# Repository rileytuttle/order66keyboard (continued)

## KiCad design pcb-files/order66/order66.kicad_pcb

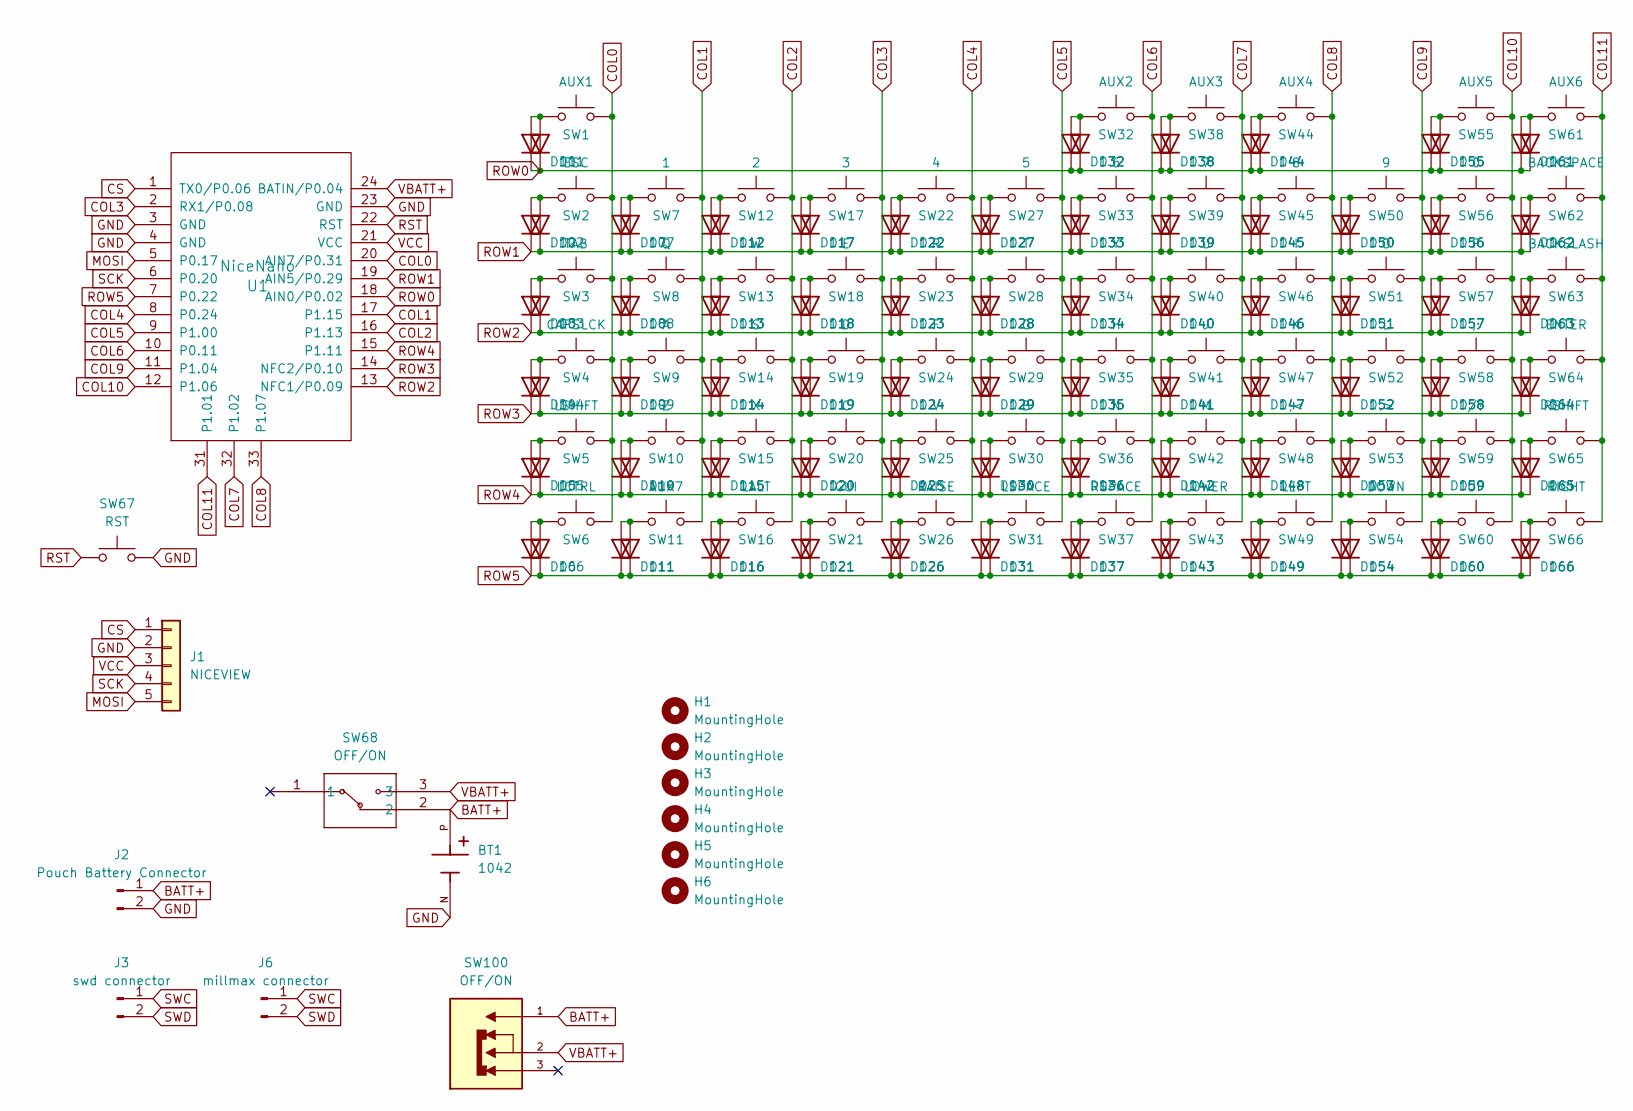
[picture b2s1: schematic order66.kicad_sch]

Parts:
BT1: 1042; BAT_1043P; PARTREV D
D1, D2, D3, D4, D5, D6, D7, D8, D9, D10, D11, D12, D13, D14, D15, D16, D17, D18, D19, D20, D21, D22, D23, D24, D25, D26, D27, D28, D29, D30, D31, D32, D33, D34, D35, D36, D37, D38, D39, D40, D41, D42, D43, D44, D45, D46, D47, D48, D49, D50, D51, D52, D53, D54, D55, D56, D57, D58, D59, D60, D61, D62, D63, D64, D65, D66: 1N4148; D_DO-35_SOD27_P7.62mm_Horizontal
D101, D102, D103, D104, D105, D106, D107, D108, D109, D110, D111, D112, D113, D114, D115, D116, D117, D118, D119, D120, D121, D122, D123, D124, D125, D126, D127, D128, D129, D130, D131, D132, D133, D134, D135, D136, D137, D138, D139, D140, D141, D142, D143, D144, D145, D146, D147, D148, D149, D150, D151, D152, D153, D154, D155, D156, D157, D158, D159, D160, D161, D162, D163, D164, D165, D166: 1N4148; D_SOD-123
H1, H2, H3, H4, H5, H6: MountingHole; MountingHole_2.7mm_M2.5
J1: NICEVIEW; PinHeader_1x05_P2.54mm_Vertical
J2: Pouch Battery Connector; JST_PH_B2B-PH-K_1x02_P2.00mm_Vertical
J3: swd connector; PinHeader_1x02_P2.54mm_Horizontal
J6: millmax connector; PinHeader_1x02_P2.54mm_Vertical
SW1: AUX1; MX-Hotswap-1U
SW2: ESC; MX-Hotswap-1U
SW3: TAB; MX-Hotswap-1U
SW4: CAPSLCK; MX-Hotswap-1U
SW5: LSHIFT; MX-Hotswap-1U
SW6: LCTRL; MX-Hotswap-1U
SW7: 1; MX-Hotswap-1U
SW8: Q; MX-Hotswap-1U
SW9: A; MX-Hotswap-1U
SW10: Z; MX-Hotswap-1U
SW11: AUX7; MX-Hotswap-1U
SW12: 2; MX-Hotswap-1U
SW13: W; MX-Hotswap-1U
SW14: S; MX-Hotswap-1U
SW15: X; MX-Hotswap-1U
SW16: LALT; MX-Hotswap-1U
SW17: 3; MX-Hotswap-1U
SW18: E; MX-Hotswap-1U
SW19: D; MX-Hotswap-1U
SW20: C; MX-Hotswap-1U
SW21: GUI; MX-Hotswap-1U
SW22: 4; MX-Hotswap-1U
SW23: R; MX-Hotswap-1U
SW24: F; MX-Hotswap-1U
SW25: V; MX-Hotswap-1U
SW26: RAISE; MX-Hotswap-1U
SW27: 5; MX-Hotswap-1U
SW28: T; MX-Hotswap-1U
SW29: G; MX-Hotswap-1U
SW30: B; MX-Hotswap-1U
SW31: LSPACE; MX-Hotswap-1U
SW32: AUX2; MX-Hotswap-1U
SW33: 6; MX-Hotswap-1U
SW34: Y; MX-Hotswap-1U
SW35: H; MX-Hotswap-1U
SW36: N; MX-Hotswap-1U
SW37: RSPACE; MX-Hotswap-1U
SW38: AUX3; MX-Hotswap-1U
SW39: 7; MX-Hotswap-1U
SW40: U; MX-Hotswap-1U
SW41: J; MX-Hotswap-1U
SW42: M; MX-Hotswap-1U
SW43: LOWER; MX-Hotswap-1U
SW44: AUX4; MX-Hotswap-1U
SW45: 8; MX-Hotswap-1U
SW46: I; MX-Hotswap-1U
SW47: K; MX-Hotswap-1U
SW48: ,<; MX-Hotswap-1U
SW49: LEFT; MX-Hotswap-1U
SW50: 9; MX-Hotswap-1U
SW51: O; MX-Hotswap-1U
SW52: L; MX-Hotswap-1U
SW53: .>; MX-Hotswap-1U
SW54: DOWN; MX-Hotswap-1U
SW55: AUX5; MX-Hotswap-1U
SW56: 0; MX-Hotswap-1U
SW57: P; MX-Hotswap-1U
SW58: ;:; MX-Hotswap-1U
SW59: /?; MX-Hotswap-1U
SW60: UP; MX-Hotswap-1U
SW61: AUX6; MX-Hotswap-1U
SW62: BACKSPACE; MX-Hotswap-1U
SW63: BACKSLASH; MX-Hotswap-1U
SW64: ENTER; MX-Hotswap-1U
SW65: RSHIFT; MX-Hotswap-1U
SW66: RIGHT; MX-Hotswap-1U
SW67: RST; SW_TH_Tactile_Omron_B3F-10xx
SW68: OFF/ON; EG1206A_EWI
SW100: OFF/ON; SW_SSSS811101; PARTREV N/A
U1: NiceNano; nice_nano

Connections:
BATT+: BT1.P, J2.1, SW68.2, SW100.1
COL0: SW1.2, SW2.2, SW3.2, SW4.2, SW5.2, SW6.2, U1.20 (AIN7/P0.31)
COL1: SW7.2, SW8.2, SW9.2, SW10.2, SW11.2, U1.17 (P1.15)
COL2: SW12.2, SW13.2, SW14.2, SW15.2, SW16.2, U1.16 (P1.13)
COL3: SW17.2, SW18.2, SW19.2, SW20.2, SW21.2, U1.2 (RX1/P0.08)
COL4: SW22.2, SW23.2, SW24.2, SW25.2, SW26.2, U1.8 (P0.24)
COL5: SW27.2, SW28.2, SW29.2, SW30.2, SW31.2, U1.9 (P1.00)
COL6: SW32.2, SW33.2, SW34.2, SW35.2, SW36.2, SW37.2, U1.10 (P0.11)
COL7: SW38.2, SW39.2, SW40.2, SW41.2, SW42.2, SW43.2, U1.32 (P1.02)
COL8: SW44.2, SW45.2, SW46.2, SW47.2, SW48.2, SW49.2, U1.33 (P1.07)
COL9: SW50.2, SW51.2, SW52.2, SW53.2, SW54.2, U1.11 (P1.04)
COL10: SW55.2, SW56.2, SW57.2, SW58.2, SW59.2, SW60.2, U1.12 (P1.06)
COL11: SW61.2, SW62.2, SW63.2, SW64.2, SW65.2, SW66.2, U1.31 (P1.01)
CS: J1.1, U1.1 (TX0/P0.06)
GND: BT1.N, J1.2, J2.2, SW67.2, U1.3 (GND), U1.4 (GND), U1.23 (GND)
MOSI: J1.5, U1.5 (P0.17)
unnamed: D1.2 (A), D101.2 (A), SW1.1
unnamed: D10.2 (A), D110.2 (A), SW10.1
unnamed: D11.2 (A), D111.2 (A), SW11.1
unnamed: D2.2 (A), D102.2 (A), SW2.1
unnamed: D3.2 (A), D103.2 (A), SW3.1
unnamed: D4.2 (A), D104.2 (A), SW4.1
unnamed: D5.2 (A), D105.2 (A), SW5.1
unnamed: D6.2 (A), D106.2 (A), SW6.1
unnamed: D7.2 (A), D107.2 (A), SW7.1
unnamed: D8.2 (A), D108.2 (A), SW8.1
unnamed: D9.2 (A), D109.2 (A), SW9.1
unnamed: D12.2 (A), D112.2 (A), SW12.1
unnamed: D13.2 (A), D113.2 (A), SW13.1
unnamed: D14.2 (A), D114.2 (A), SW14.1
unnamed: D15.2 (A), D115.2 (A), SW15.1
unnamed: D16.2 (A), D116.2 (A), SW16.1
unnamed: D17.2 (A), D117.2 (A), SW17.1
unnamed: D18.2 (A), D118.2 (A), SW18.1
unnamed: D19.2 (A), D119.2 (A), SW19.1
unnamed: D20.2 (A), D120.2 (A), SW20.1
unnamed: D21.2 (A), D121.2 (A), SW21.1
unnamed: D22.2 (A), D122.2 (A), SW22.1
unnamed: D23.2 (A), D123.2 (A), SW23.1
unnamed: D24.2 (A), D124.2 (A), SW24.1
unnamed: D25.2 (A), D125.2 (A), SW25.1
unnamed: D26.2 (A), D126.2 (A), SW26.1
unnamed: D27.2 (A), D127.2 (A), SW27.1
unnamed: D28.2 (A), D128.2 (A), SW28.1
unnamed: D29.2 (A), D129.2 (A), SW29.1
unnamed: D30.2 (A), D130.2 (A), SW30.1
unnamed: D31.2 (A), D131.2 (A), SW31.1
unnamed: D32.2 (A), D132.2 (A), SW32.1
unnamed: D33.2 (A), D133.2 (A), SW33.1
unnamed: D34.2 (A), D134.2 (A), SW34.1
unnamed: D35.2 (A), D135.2 (A), SW35.1
unnamed: D36.2 (A), D136.2 (A), SW36.1
unnamed: D37.2 (A), D137.2 (A), SW37.1
unnamed: D38.2 (A), D138.2 (A), SW38.1
unnamed: D39.2 (A), D139.2 (A), SW39.1
unnamed: D40.2 (A), D140.2 (A), SW40.1
unnamed: D41.2 (A), D141.2 (A), SW41.1
unnamed: D42.2 (A), D142.2 (A), SW42.1
unnamed: D43.2 (A), D143.2 (A), SW43.1
unnamed: D44.2 (A), D144.2 (A), SW44.1
unnamed: D45.2 (A), D145.2 (A), SW45.1
unnamed: D46.2 (A), D146.2 (A), SW46.1
unnamed: D47.2 (A), D147.2 (A), SW47.1
unnamed: D48.2 (A), D148.2 (A), SW48.1
unnamed: D49.2 (A), D149.2 (A), SW49.1
unnamed: D50.2 (A), D150.2 (A), SW50.1
unnamed: D51.2 (A), D151.2 (A), SW51.1
unnamed: D52.2 (A), D152.2 (A), SW52.1
unnamed: D53.2 (A), D153.2 (A), SW53.1
unnamed: D54.2 (A), D154.2 (A), SW54.1
unnamed: D55.2 (A), D155.2 (A), SW55.1
unnamed: D56.2 (A), D156.2 (A), SW56.1
unnamed: D57.2 (A), D157.2 (A), SW57.1
unnamed: D58.2 (A), D158.2 (A), SW58.1
unnamed: D59.2 (A), D159.2 (A), SW59.1
unnamed: D60.2 (A), D160.2 (A), SW60.1
unnamed: D61.2 (A), D161.2 (A), SW61.1
unnamed: D62.2 (A), D162.2 (A), SW62.1
unnamed: D63.2 (A), D163.2 (A), SW63.1
unnamed: D64.2 (A), D164.2 (A), SW64.1
unnamed: D65.2 (A), D165.2 (A), SW65.1
unnamed: D66.2 (A), D166.2 (A), SW66.1
ROW0: D1.1 (K), D32.1 (K), D38.1 (K), D44.1 (K), D55.1 (K), D61.1 (K), D101.1 (K), D132.1 (K), D138.1 (K), D144.1 (K), D155.1 (K), D161.1 (K), U1.18 (AIN0/P0.02)
ROW1: D2.1 (K), D7.1 (K), D12.1 (K), D17.1 (K), D22.1 (K), D27.1 (K), D33.1 (K), D39.1 (K), D45.1 (K), D50.1 (K), D56.1 (K), D62.1 (K), D102.1 (K), D107.1 (K), D112.1 (K), D117.1 (K), D122.1 (K), D127.1 (K), D133.1 (K), D139.1 (K), D145.1 (K), D150.1 (K), D156.1 (K), D162.1 (K), U1.19 (AIN5/P0.29)
ROW2: D3.1 (K), D8.1 (K), D13.1 (K), D18.1 (K), D23.1 (K), D28.1 (K), D34.1 (K), D40.1 (K), D46.1 (K), D51.1 (K), D57.1 (K), D63.1 (K), D103.1 (K), D108.1 (K), D113.1 (K), D118.1 (K), D123.1 (K), D128.1 (K), D134.1 (K), D140.1 (K), D146.1 (K), D151.1 (K), D157.1 (K), D163.1 (K), U1.13 (NFC1/P0.09)
ROW3: D4.1 (K), D9.1 (K), D14.1 (K), D19.1 (K), D24.1 (K), D29.1 (K), D35.1 (K), D41.1 (K), D47.1 (K), D52.1 (K), D58.1 (K), D64.1 (K), D104.1 (K), D109.1 (K), D114.1 (K), D119.1 (K), D124.1 (K), D129.1 (K), D135.1 (K), D141.1 (K), D147.1 (K), D152.1 (K), D158.1 (K), D164.1 (K), U1.14 (NFC2/P0.10)
ROW4: D5.1 (K), D10.1 (K), D15.1 (K), D20.1 (K), D25.1 (K), D30.1 (K), D36.1 (K), D42.1 (K), D48.1 (K), D53.1 (K), D59.1 (K), D65.1 (K), D105.1 (K), D110.1 (K), D115.1 (K), D120.1 (K), D125.1 (K), D130.1 (K), D136.1 (K), D142.1 (K), D148.1 (K), D153.1 (K), D159.1 (K), D165.1 (K), U1.15 (P1.11)
ROW5: D6.1 (K), D11.1 (K), D16.1 (K), D21.1 (K), D26.1 (K), D31.1 (K), D37.1 (K), D43.1 (K), D49.1 (K), D54.1 (K), D60.1 (K), D66.1 (K), D106.1 (K), D111.1 (K), D116.1 (K), D121.1 (K), D126.1 (K), D131.1 (K), D137.1 (K), D143.1 (K), D149.1 (K), D154.1 (K), D160.1 (K), D166.1 (K), U1.7 (P0.22)
RST: SW67.1, U1.22 (RST)
SCK: J1.4, U1.6 (P0.20)
SWC: J3.1, J6.1
SWD: J3.2, J6.2
VBATT+: SW68.3, SW100.2, U1.24 (BATIN/P0.04)
VCC: J1.3, U1.21 (VCC)

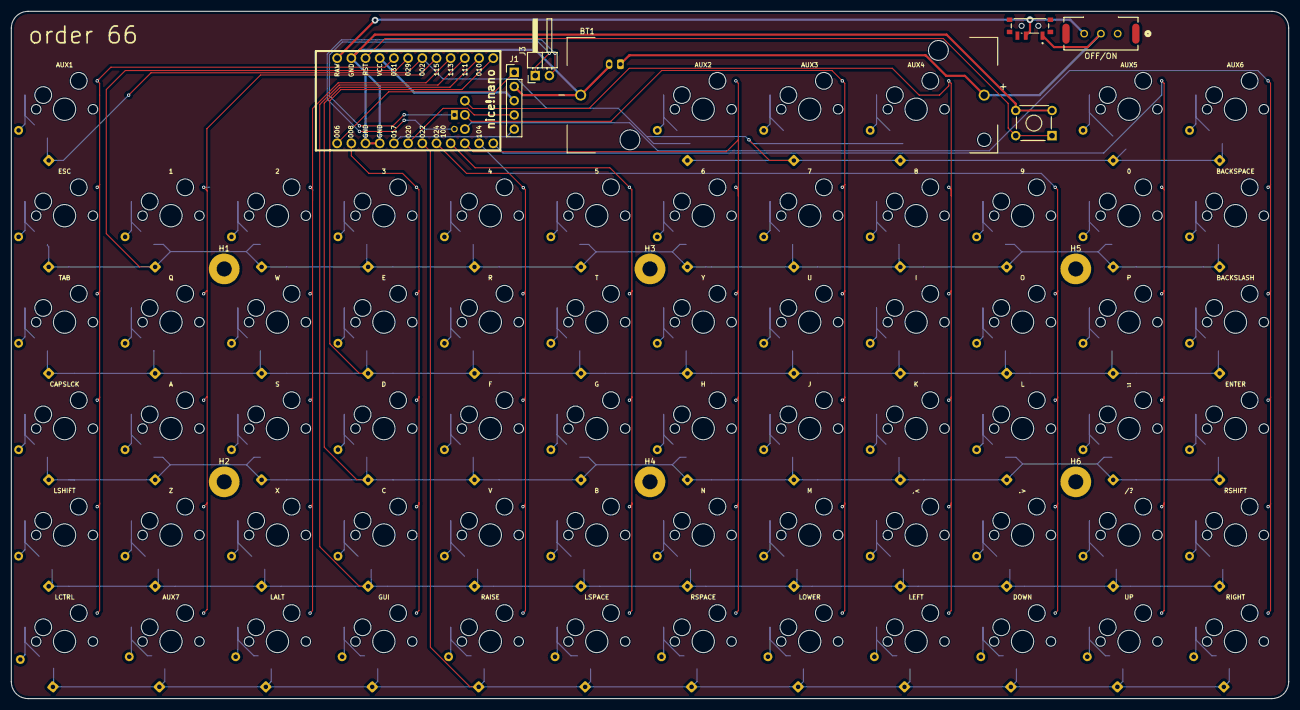
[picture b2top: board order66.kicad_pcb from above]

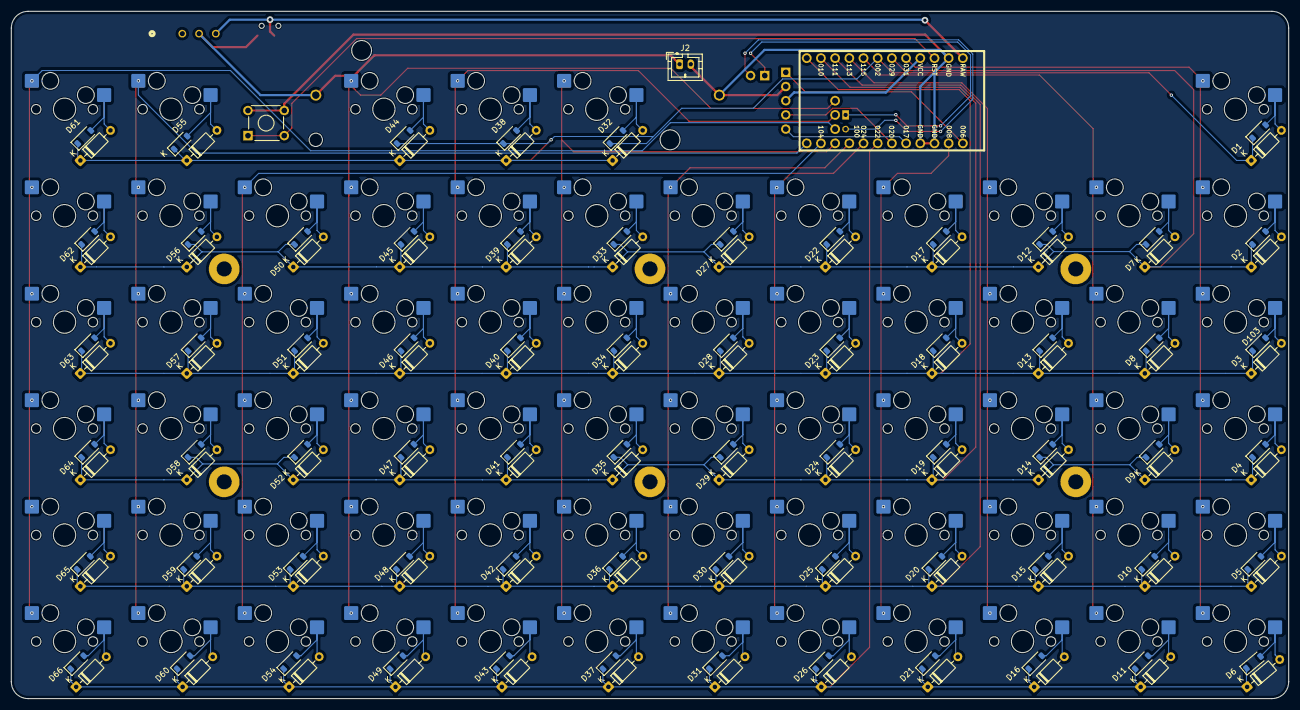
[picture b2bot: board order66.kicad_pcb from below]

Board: 2 copper layers, 228.6 x 123.0 mm, 213 parts (199 on the bottom side), 94 nets.

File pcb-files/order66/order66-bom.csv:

"Reference","Value","Datasheet","Footprint","Qty","DNP"
"BT1","1042","","1043P:BAT_1043P","1",""
"D1,D2,D3,D4,D5,D6,D7,D8,D9,D10,D11,D12,D13,D14,D15,D16,D17,D18,D19,D20,D21,D22,D23,D24,D25,D26,D27,D28,D29,D30,D31,D32,D33,D34,D35,D36,D37,D38,D39,D40,D41,D42,D43,D44,D45,D46,D47,D48,D49,D50,D51,D52,D53,D54,D55,D56,D57,D58,D59,D60,D61,D62,D63,D64,D65,D66,D101,D102,D103,D104,D105,D106,D107,D108,D109,D110,D111,D112,D113,D114,D115,D116,D117,D118,D119,D120,D121,D122,D123,D124,D125,D126,D127,D128,D129,D130,D131,D132,D133,D134,D135,D136,D137,D138,D139,D140,D141,D142,D143,D144,D145,D146,D147,D148,D149,D150,D151,D152,D153,D154,D155,D156,D157,D158,D159,D160,D161,D162,D163,D164,D165,D166","1N4148","https://assets.nexperia.com/documents/data-sheet/1N4148_1N4448.pdf,https://www.vishay.com/docs/85748/1n4148w.pdf","Diode_SMD:D_SOD-123,Diode_THT:D_DO-35_SOD27_P7.62mm_Horizontal","132",""
"J1","NICEVIEW","~","Connector_PinHeader_2.54mm:PinHeader_1x05_P2.54mm_Vertical","1",""
"J2","Pouch Battery Connector","~","Connector_JST:JST_PH_B2B-PH-K_1x02_P2.00mm_Vertical","1",""
"J3","swd connector","~","Connector_PinHeader_2.54mm:PinHeader_1x02_P2.54mm_Horizontal","1",""
"J6","millmax connector","~","Connector_PinHeader_2.54mm:PinHeader_1x02_P2.54mm_Vertical","1",""
"SW1","AUX1","~","MX_Hotswap:MX-Hotswap-1U","1",""
"SW2","ESC","~","MX_Hotswap:MX-Hotswap-1U","1",""
"SW3","TAB","~","MX_Hotswap:MX-Hotswap-1U","1",""
"SW4","CAPSLCK","~","MX_Hotswap:MX-Hotswap-1U","1",""
"SW5","LSHIFT","~","MX_Hotswap:MX-Hotswap-1U","1",""
"SW6","LCTRL","~","MX_Hotswap:MX-Hotswap-1U","1",""
"SW7","1","~","MX_Hotswap:MX-Hotswap-1U","1",""
"SW8","Q","~","MX_Hotswap:MX-Hotswap-1U","1",""
"SW9","A","~","MX_Hotswap:MX-Hotswap-1U","1",""
"SW10","Z","~","MX_Hotswap:MX-Hotswap-1U","1",""
"SW11","AUX7","~","MX_Hotswap:MX-Hotswap-1U","1",""
"SW12","2","~","MX_Hotswap:MX-Hotswap-1U","1",""
"SW13","W","~","MX_Hotswap:MX-Hotswap-1U","1",""
"SW14","S","~","MX_Hotswap:MX-Hotswap-1U","1",""
"SW15","X","~","MX_Hotswap:MX-Hotswap-1U","1",""
"SW16","LALT","~","MX_Hotswap:MX-Hotswap-1U","1",""
"SW17","3","~","MX_Hotswap:MX-Hotswap-1U","1",""
"SW18","E","~","MX_Hotswap:MX-Hotswap-1U","1",""
"SW19","D","~","MX_Hotswap:MX-Hotswap-1U","1",""
"SW20","C","~","MX_Hotswap:MX-Hotswap-1U","1",""
"SW21","GUI","~","MX_Hotswap:MX-Hotswap-1U","1",""
"SW22","4","~","MX_Hotswap:MX-Hotswap-1U","1",""
"SW23","R","~","MX_Hotswap:MX-Hotswap-1U","1",""
"SW24","F","~","MX_Hotswap:MX-Hotswap-1U","1",""
"SW25","V","~","MX_Hotswap:MX-Hotswap-1U","1",""
"SW26","RAISE","~","MX_Hotswap:MX-Hotswap-1U","1",""
"SW27","5","~","MX_Hotswap:MX-Hotswap-1U","1",""
"SW28","T","~","MX_Hotswap:MX-Hotswap-1U","1",""
"SW29","G","~","MX_Hotswap:MX-Hotswap-1U","1",""
"SW30","B","~","MX_Hotswap:MX-Hotswap-1U","1",""
"SW31","LSPACE","~","MX_Hotswap:MX-Hotswap-1U","1",""
"SW32","AUX2","~","MX_Hotswap:MX-Hotswap-1U","1",""
"SW33","6","~","MX_Hotswap:MX-Hotswap-1U","1",""
"SW34","Y","~","MX_Hotswap:MX-Hotswap-1U","1",""
"SW35","H","~","MX_Hotswap:MX-Hotswap-1U","1",""
"SW36","N","~","MX_Hotswap:MX-Hotswap-1U","1",""
"SW37","RSPACE","~","MX_Hotswap:MX-Hotswap-1U","1",""
"SW38","AUX3","~","MX_Hotswap:MX-Hotswap-1U","1",""
"SW39","7","~","MX_Hotswap:MX-Hotswap-1U","1",""
"SW40","U","~","MX_Hotswap:MX-Hotswap-1U","1",""
"SW41","J","~","MX_Hotswap:MX-Hotswap-1U","1",""
"SW42","M","~","MX_Hotswap:MX-Hotswap-1U","1",""
"SW43","LOWER","~","MX_Hotswap:MX-Hotswap-1U","1",""
"SW44","AUX4","~","MX_Hotswap:MX-Hotswap-1U","1",""
"SW45","8","~","MX_Hotswap:MX-Hotswap-1U","1",""
"SW46","I","~","MX_Hotswap:MX-Hotswap-1U","1",""
"SW47","K","~","MX_Hotswap:MX-Hotswap-1U","1",""
"SW48",",<","~","MX_Hotswap:MX-Hotswap-1U","1",""
"SW49","LEFT","~","MX_Hotswap:MX-Hotswap-1U","1",""
"SW50","9","~","MX_Hotswap:MX-Hotswap-1U","1",""
"SW51","O","~","MX_Hotswap:MX-Hotswap-1U","1",""
"SW52","L","~","MX_Hotswap:MX-Hotswap-1U","1",""
"SW53",".>","~","MX_Hotswap:MX-Hotswap-1U","1",""
"SW54","DOWN","~","MX_Hotswap:MX-Hotswap-1U","1",""
"SW55","AUX5","~","MX_Hotswap:MX-Hotswap-1U","1",""
"SW56","0","~","MX_Hotswap:MX-Hotswap-1U","1",""
"SW57","P","~","MX_Hotswap:MX-Hotswap-1U","1",""
"SW58",";:","~","MX_Hotswap:MX-Hotswap-1U","1",""
"SW59","/?","~","MX_Hotswap:MX-Hotswap-1U","1",""
"SW60","UP","~","MX_Hotswap:MX-Hotswap-1U","1",""
"SW61","AUX6","~","MX_Hotswap:MX-Hotswap-1U","1",""
"SW62","BACKSPACE","~","MX_Hotswap:MX-Hotswap-1U","1",""
"SW63","BACKSLASH","~","MX_Hotswap:MX-Hotswap-1U","1",""
"SW64","ENTER","~","MX_Hotswap:MX-Hotswap-1U","1",""
"SW65","RSHIFT","~","MX_Hotswap:MX-Hotswap-1U","1",""
"SW66","RIGHT","~","MX_Hotswap:MX-Hotswap-1U","1",""
"SW67","RST","~","Button_Switch_THT:SW_TH_Tactile_Omron_B3F-10xx","1",""
"SW68,SW100","OFF/ON","EG1206A","SSSS811101:SW_SSSS811101,footprints:EG1206A_EWI","2",""
"U1","NiceNano","","nice-nano-kicad:nice_nano","1",""

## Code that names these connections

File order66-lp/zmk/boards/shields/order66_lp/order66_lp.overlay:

/*
 * order66-lp: 5x12 Kailh Choc v1 ortholinear, split by a 54 mm central
 * band, plus two dedicated mouse buttons beside a Cirque trackpad.
 *
 * GENERATED by tools/gen_overlay.py from the same NANO_NETS/el_pos() that build the
 * schematic -- edit those, not this file.
 *
 * SPDX-License-Identifier: MIT
 *
 * Matrix: 11 rows x 6 cols = 66 positions, 62 used.
 * Same 17 pins as a 5x12 but six more positions, which is what pays for the mouse
 * buttons. Electrical columns are shared by both halves; each half owns a block of
 * rows, so row nets stay local to one half instead of spanning the board:
 *
 *   left  half, physical cols 0-5   -> rows 0-4,  cols 0-5
 *   right half, physical cols 6-11  -> rows 5-9,  cols 0-5
 *   mouse buttons                   -> row 10,   cols 0-1
 *   spare                           -> row 10,   cols 2-5
 *
 * The physical layout is defined here rather than including ZMK's shared
 * layouts/common/ortho_5x12 -- that one has no central gap, and patching it is what
 * forced the v1.0 board's ZMK fork. A layout in our own module needs no fork.
 */

#include <dt-bindings/zmk/matrix_transform.h>
#include <physical_layouts.dtsi>

/ {
    chosen {
        zmk,kscan = &kscan0;
        zmk,physical-layout = &layout_order66_lp;
    };

    layout_order66_lp: layout_order66_lp {
        compatible = "zmk,physical-layout";
        display-name = "order66-lp";
        transform = <&matrix_transform_order66_lp>;

        keys  //                     w   h    x    y     rot    rx    ry
            = <&key_physical_attrs 100 100    0    0       0     0     0>
            , <&key_physical_attrs 100 100  100    0       0     0     0>
            , <&key_physical_attrs 100 100  200    0       0     0     0>
            , <&key_physical_attrs 100 100  300    0       0     0     0>
            , <&key_physical_attrs 100 100  400    0       0     0     0>
            , <&key_physical_attrs 100 100  500    0       0     0     0>
            , <&key_physical_attrs 100 100  900    0       0     0     0>
            , <&key_physical_attrs 100 100 1000    0       0     0     0>
            , <&key_physical_attrs 100 100 1100    0       0     0     0>
            , <&key_physical_attrs 100 100 1200    0       0     0     0>
            , <&key_physical_attrs 100 100 1300    0       0     0     0>
            , <&key_physical_attrs 100 100 1400    0       0     0     0>
            , <&key_physical_attrs 100 100    0  100       0     0     0>
            , <&key_physical_attrs 100 100  100  100       0     0     0>
            , <&key_physical_attrs 100 100  200  100       0     0     0>
            , <&key_physical_attrs 100 100  300  100       0     0     0>
            , <&key_physical_attrs 100 100  400  100       0     0     0>
            , <&key_physical_attrs 100 100  500  100       0     0     0>
            , <&key_physical_attrs 100 100  900  100       0     0     0>
            , <&key_physical_attrs 100 100 1000  100       0     0     0>
            , <&key_physical_attrs 100 100 1100  100       0     0     0>
            , <&key_physical_attrs 100 100 1200  100       0     0     0>
            , <&key_physical_attrs 100 100 1300  100       0     0     0>
            , <&key_physical_attrs 100 100 1400  100       0     0     0>
            , <&key_physical_attrs 100 100    0  200       0     0     0>
            , <&key_physical_attrs 100 100  100  200       0     0     0>
            , <&key_physical_attrs 100 100  200  200       0     0     0>
            , <&key_physical_attrs 100 100  300  200       0     0     0>
            , <&key_physical_attrs 100 100  400  200       0     0     0>
            , <&key_physical_attrs 100 100  500  200       0     0     0>
            , <&key_physical_attrs 100 100  900  200       0     0     0>
            , <&key_physical_attrs 100 100 1000  200       0     0     0>
            , <&key_physical_attrs 100 100 1100  200       0     0     0>
            , <&key_physical_attrs 100 100 1200  200       0     0     0>
            , <&key_physical_attrs 100 100 1300  200       0     0     0>
            , <&key_physical_attrs 100 100 1400  200       0     0     0>
            , <&key_physical_attrs 100 100    0  300       0     0     0>
            , <&key_physical_attrs 100 100  100  300       0     0     0>
            , <&key_physical_attrs 100 100  200  300       0     0     0>
            , <&key_physical_attrs 100 100  300  300       0     0     0>
            , <&key_physical_attrs 100 100  400  300       0     0     0>
            , <&key_physical_attrs 100 100  500  300       0     0     0>
            , <&key_physical_attrs 100 100  900  300       0     0     0>
            , <&key_physical_attrs 100 100 1000  300       0     0     0>
            , <&key_physical_attrs 100 100 1100  300       0     0     0>
            , <&key_physical_attrs 100 100 1200  300       0     0     0>
            , <&key_physical_attrs 100 100 1300  300       0     0     0>
            , <&key_physical_attrs 100 100 1400  300       0     0     0>
            , <&key_physical_attrs 100 100    0  400       0     0     0>
            , <&key_physical_attrs 100 100  100  400       0     0     0>
            , <&key_physical_attrs 100 100  200  400       0     0     0>
            , <&key_physical_attrs 100 100  300  400       0     0     0>
            , <&key_physical_attrs 100 100  400  400       0     0     0>
            , <&key_physical_attrs 100 100  500  400       0     0     0>
            , <&key_physical_attrs 100 100  900  400       0     0     0>
            , <&key_physical_attrs 100 100 1000  400       0     0     0>
            , <&key_physical_attrs 100 100 1100  400       0     0     0>
            , <&key_physical_attrs 100 100 1200  400       0     0     0>
            , <&key_physical_attrs 100 100 1300  400       0     0     0>
            , <&key_physical_attrs 100 100 1400  400       0     0     0>
            , <&key_physical_attrs 100 100  575  400       0     0     0>
            , <&key_physical_attrs 100 100  675  400       0     0     0>
            ;
    };

    matrix_transform_order66_lp: keymap_transform_0 {
        compatible = "zmk,matrix-transform";
        columns = <6>;
        rows = <11>;
        map = <
            RC(0,0) RC(0,1) RC(0,2) RC(0,3) RC(0,4) RC(0,5)   RC(5,0) RC(5,1) RC(5,2) RC(5,3) RC(5,4) RC(5,5)
            RC(1,0) RC(1,1) RC(1,2) RC(1,3) RC(1,4) RC(1,5)   RC(6,0) RC(6,1) RC(6,2) RC(6,3) RC(6,4) RC(6,5)
            RC(2,0) RC(2,1) RC(2,2) RC(2,3) RC(2,4) RC(2,5)   RC(7,0) RC(7,1) RC(7,2) RC(7,3) RC(7,4) RC(7,5)
            RC(3,0) RC(3,1) RC(3,2) RC(3,3) RC(3,4) RC(3,5)   RC(8,0) RC(8,1) RC(8,2) RC(8,3) RC(8,4) RC(8,5)
            RC(4,0) RC(4,1) RC(4,2) RC(4,3) RC(4,4) RC(4,5)   RC(9,0) RC(9,1) RC(9,2) RC(9,3) RC(9,4) RC(9,5)
            RC(10,0) RC(10,1)   // mouse buttons
            >;
    };

    kscan0: kscan {
        compatible = "zmk,kscan-gpio-matrix";
        wakeup-source;

        diode-direction = "col2row";

        row-gpios
            = <&gpio0 29 (GPIO_ACTIVE_HIGH | GPIO_PULL_DOWN)> // ROW0
            , <&gpio0 9 (GPIO_ACTIVE_HIGH | GPIO_PULL_DOWN)> // ROW1
            , <&gpio0 10 (GPIO_ACTIVE_HIGH | GPIO_PULL_DOWN)> // ROW2
            , <&gpio1 11 (GPIO_ACTIVE_HIGH | GPIO_PULL_DOWN)> // ROW3
            , <&gpio0 22 (GPIO_ACTIVE_HIGH | GPIO_PULL_DOWN)> // ROW4
            , <&gpio0 11 (GPIO_ACTIVE_HIGH | GPIO_PULL_DOWN)> // ROW5
            , <&gpio1 2 (GPIO_ACTIVE_HIGH | GPIO_PULL_DOWN)> // ROW6
            , <&gpio1 7 (GPIO_ACTIVE_HIGH | GPIO_PULL_DOWN)> // ROW7
            , <&gpio1 4 (GPIO_ACTIVE_HIGH | GPIO_PULL_DOWN)> // ROW8
            , <&gpio1 6 (GPIO_ACTIVE_HIGH | GPIO_PULL_DOWN)> // ROW9
            , <&gpio1 1 (GPIO_ACTIVE_HIGH | GPIO_PULL_DOWN)> // ROW10
            ;

        col-gpios
            = <&gpio0 31 GPIO_ACTIVE_HIGH> // COL0
            , <&gpio1 15 GPIO_ACTIVE_HIGH> // COL1
            , <&gpio1 13 GPIO_ACTIVE_HIGH> // COL2
            , <&gpio0 8 GPIO_ACTIVE_HIGH> // COL3
            , <&gpio0 24 GPIO_ACTIVE_HIGH> // COL4
            , <&gpio1 0 GPIO_ACTIVE_HIGH> // COL5
            ;
    };
};

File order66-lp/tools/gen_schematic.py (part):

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}

# nice!nano v2 pin -> net. Columns are unchanged from the v1.0 board; rows are the old
# ROW1..ROW5 renumbered after dropping the 6-key top row.
NANO_NETS = {
    # All 21 exposed GPIO are used: 6 columns + 11 rows + LED data + I2C + data-ready.
    # COL0-5 and ROW0-4 keep the pins they had on the 5x12 board; the old COL6-11 pins
    # become the right half's ROW5-10, so this is a minimal remap rather than a reshuffle.
    1:  'LED_DIN_3V3',   # TX0/P0.06  -- SPIM3 MOSI for the backlight chain
    2:  'COL3',          # RX1/P0.08
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        at = (x0b + c * px, y0b + r * py)
        s.symbol(C, f'C{101 + i}', at, value='100n', footprint=FP_C,
                 ref_offset=(-6.35, -2.54), val_offset=(-6.35, 2.54), hide_value=(c > 0))
        s.vstub('VLED', s.pin(C, at, 1), 6.35, 'up')
        s.vstub('GND', s.pin(C, at, 2), 6.35, 'down')


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    for ref, pos, fp, note in (('J2', (701.04, 205.74), FP_HDR2H, 'SWD horizontal'),
                               ('J3', (701.04, 228.6), FP_HDR2, 'SWD millmax vertical')):
        s.symbol(CONN2, ref, pos, value=note, footprint=fp)
        s.stub('SWC', s.pin(CONN2, pos, 1), 7.62, 'right')
        s.stub('SWD', s.pin(CONN2, pos, 2), 7.62, 'right')


# ---------------------------------------------------------------- LED power
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
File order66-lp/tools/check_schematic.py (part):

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          f'all 21 exposed GPIO assigned exactly once (found {len(gpio)})')
    check(nano_pins.get('24') == 'VBATT+', f"BATIN on VBATT+ (got {nano_pins.get('24')})")
    check(nano_pins.get('21') == 'VCC', f"VCC pin on VCC (got {nano_pins.get('21')})")
    check(nano_pins.get('1') == 'LED_DIN_3V3',
          f"P0.06 drives the LED chain (got {nano_pins.get('1')})")

    # ---------------------------------------------------------------- trackpad
    print('\ntrackpad')
    for ref, pin, want_net, desc in (
            ('J4', '9', 'TP_SCL', 'FFC pin 9 is SCL'),
            ('J4', '10', 'TP_SDA', 'FFC pin 10 is SDA'),
            ('J4', '11', 'GND', 'FFC pin 11 is GND'),
            ('J4', '12', 'VCC', 'FFC pin 12 is VDD, on the switchable rail'),
            ('J4', '4', 'TP_DR', 'FFC pin 4 is data-ready')):
        got = net_of(nets, ref, pin)
        check(got == want_net, f'{desc} ({ref}.{pin} = {got})')
    # KiCad names a no-connect pin's net 'unconnected-(J4-PadN)' rather than leaving
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
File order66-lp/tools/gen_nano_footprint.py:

#!/usr/bin/env python3
"""
Derive a mixed through-hole / surface-mount nice!nano footprint.

The nano is socketed on headers rather than soldered flat, and the two pad rows
(15.24 mm apart) cannot both be through-hole on this board: a THT pin emerges on the
top face, where the free band between switch bodies is only 3.00 mm, while the
bottom-side band is 7.70 mm. With rows 15.24 mm apart on a 17 mm row pitch the two
are 1.76 mm out of step, so only one row can be through-hole. Making the other row
surface-mount removes its top-side constraint entirely.

  pins 1-12   -> through-hole   (one long edge; sneaks between key columns)
  pins 13-24  -> surface-mount  (the other long edge)
  pins 31-33  -> surface-mount  (interior pads; see the note below)

Pins 31/32/33 sit at x=+8.89, y=0/2.54/5.08 -- under the middle of the module, not on
either edge row. An edge header cannot reach them, so they need their own 1x3 header
beneath the nano. They are included here only so the footprint still matches the
27-pin symbol. The tidier fix is to move their three nets (COL7, COL8, COL11) onto the
three unused pro_micro connector pins, which also makes the shield portable to any
pro_micro-footprint controller.

Source footprint is the vendored nice-nano-kicad one, left untouched.

Run: python3 tools/gen_nano_footprint.py
"""
import os
import sys

HERE = os.path.dirname(os.path.abspath(__file__))
ROOT = os.path.dirname(HERE)
sys.path.insert(0, HERE)
from sexpr import parse, dump, get, getall, Str  # noqa: E402
from schlib import uid, n  # noqa: E402

SRC = os.path.join(ROOT, 'libraries/nice-nano-kicad/nice_nano.kicad_mod')
OUTDIR = os.path.join(ROOT, 'libraries/order66lp.pretty')
NAME = 'nice_nano_Hdr_TH1-12_SMD13-33'
OUT = os.path.join(OUTDIR, NAME + '.kicad_mod')

TH_PINS = {str(i) for i in range(1, 13)}

# Surface-mount pad size, centred on the nominal pin position. Deliberately generous
# so it suits either an SMD 2.54 mm header's solder tail or a directly soldered pin.
# Check against the datasheet of whichever header you actually buy.
SMD_W, SMD_H = 1.6, 2.6
# Pins 31-33 run along y at 2.54 mm pitch, not along x like the edge rows. Make them
# square rather than elongated: a 2.6 mm dimension anywhere collides at 2.54 mm pitch
# once the footprint is placed at 90/270 degrees, which is exactly what happened.
INTERIOR = {'31', '32', '33'}
SMD_SQ = 1.6

DESCR = ('nice!nano v2 on headers, mixed mount: pins 1-12 through-hole, pins 13-24 '
         'and 31-33 surface-mount. For boards where a THT pin on both rows would '
         'foul the switch bodies on the opposite face. Pins 31-33 are interior pads '
         'and need their own 1x3 header. Derived from nice-nano-kicad by '
         'tools/gen_nano_footprint.py.')
TAGS = 'nice_nano nrf52840 pro_micro header mixed tht smd socketed'


def main():
    fp = parse(open(SRC).read())[0]
    out = ['(footprint "%s"' % NAME,
           '\t(version 20241229)',
           '\t(generator "gen_nano_footprint.py")',
           '\t(layer "F.Cu")',
           '\t(descr "%s")' % DESCR,
           '\t(tags "%s")' % TAGS,
           '\t(attr through_hole)']

    th = smd = 0
    body = []
    for ch in fp[1:]:
        if not isinstance(ch, list):
            continue
        h = str(ch[0])
        if h in ('version', 'generator', 'generator_version', 'layer', 'at',
                 'descr', 'tags', 'attr', 'uuid', 'tedit', 'property'):
            continue
        if h != 'pad':
            body.append(ch)
            continue

        name = str(ch[1])
        at = get(ch, 'at')
        x, y = float(at[1]), float(at[2])
        if name in TH_PINS:
            th += 1
            body.append(ch)          # keep the original through-hole pad verbatim
            continue
        smd += 1
        w, h = (SMD_SQ, SMD_SQ) if name in INTERIOR else (SMD_W, SMD_H)
        body.append(parse(
            f'(pad "{name}" smd roundrect (at {n(x)} {n(y)}) '
            f'(size {n(w)} {n(h)}) (layers "F.Cu" "F.Paste" "F.Mask") '
            f'(roundrect_rratio 0.15) (uuid "{uid("nanofp/pad/" + name)}"))')[0])

    # Mark which row is which, so it is obvious on the board.
    for text, pos in (('TH 1-12', (0, 10.8)), ('SMD 13-24', (0, -10.8))):
        body.append(parse(
            f'(fp_text user "{text}" (at {n(pos[0])} {n(pos[1])} 0) (layer "F.SilkS") '
            f'(uuid "{uid("nanofp/txt/" + text)}") '
            f'(effects (font (size 1 1) (thickness 0.15))))')[0])

    for ch in body:
        out.append(dump(ch, 1))
    out += ['\t(embedded_fonts no)', ')', '']

    # No two pads may overlap, and none may sit closer than the fab minimum.
    pads = []
    for ch in body:
        if isinstance(ch, list) and str(ch[0]) == 'pad':
            at, sz = get(ch, 'at'), get(ch, 'size')
            pads.append((str(ch[1]), float(at[1]), float(at[2]),
                         float(sz[1]), float(sz[2])))
    MIN = 0.15
    bad = []
    for i in range(len(pads)):
        for j in range(i + 1, len(pads)):
            a, b = pads[i], pads[j]
            gx = abs(a[1] - b[1]) - (a[3] + b[3]) / 2
            gy = abs(a[2] - b[2]) - (a[4] + b[4]) / 2
            if gx < MIN and gy < MIN:
                bad.append(f'pads {a[0]} and {b[0]}: gap {max(gx, gy):+.3f} mm')
    if bad:
        print(f'ERROR: {len(bad)} pad clearance problem(s):')
        for b in bad[:8]:
            print('  ' + b)
        return 1
    print(f'  pad-to-pad clearance: all >= {MIN} mm')

    os.makedirs(OUTDIR, exist_ok=True)
    open(OUT, 'w').write('\n'.join(out))
    print(f'wrote {OUT}')
    print(f'  through-hole pads : {th}  (pins 1-12)')
    print(f'  surface-mount pads: {smd} (pins 13-24, 31-33) @ {SMD_W} x {SMD_H} mm')
    return 0


if __name__ == '__main__':
    sys.exit(main())

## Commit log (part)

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2025-06-20 first commit of order66 keyboard
2025-06-23 tracking the sym lib table
2025-06-23 removed keebio library because I think its not used maybe
2025-06-23 removing unused library files
2025-06-23 fixing gitignore
2025-06-23 adding pcb images
2025-06-23 cleaning up libraries
2025-06-24 changed to through hole diodes in schematic
2025-06-24 moved to more through hole components and rerouted traces
2025-06-24 trying to generate bom
2025-06-24 reordered the switch and diode numberings to be in order
2025-06-24 fixing and checking on board design rules to match pcb fabrication
2025-06-25 starting work on case
2025-06-25 reorganizing now that case files exists
2025-06-26 added support for millmax spring loaded swd pins for bootloader support
2025-06-26 Trying though hole diodes (#1)
    * changed to through hole diodes in schematic
    * moved to more through hole components and rerouted traces
    * trying to generate bom
    * reordered the switch and diode numberings to be in order
    * fixing and checking on board design rules to match pcb fabrication
    * starting work on case
2025-06-26 added the smd sod 123 package diode symbols. havent placed/routed all the footprints yet but seems to be okay. need to figure out what I want to do with the silkscreen references. probably should jus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
2025-06-26 placed all diode footprints. need to sort out the silkscreen overlaps
2025-06-26 added the other version of power switch that I have as well just in case
2025-06-26 Trying smd and through hole diodes same time (#2)
    * added the smd sod 123 package diode symbols. havent placed/routed all the footprints yet but seems to be okay. need to figure out what I want to do with the silkscreen references. probably should j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
    * placed all diode footprints. need to sort out the silkscreen overlaps
    * added the other version of power switch that I have as well just in case
2025-06-26 updated pcb front back images and bom
2025-06-30 adding both an order 66 logo and a connector for the jlink but that needs work
2025-06-30 removing the connector for the link for now
2025-07-01 suring up before pcb fab
2025-07-08 rough keyboard case design. needs pcb to test out with
2025-07-09 adding some more dimensions to the pcb to aid case design
2025-07-18 fixes #5: fixing the switch pass through in case
2025-07-18 Working on case after receiving pcb (#10)
    * adds the case and keygrid
    * fixes #5: fixing the switch pass through in case
2025-07-18 fixes #11: using flathead screws for the case
2025-07-18 fixes #11: using flathead screws for the case (#12)
2025-07-21 separating all required order 66 keyboard files into different repos to help with versioning
2025-07-21 separating all required order 66 keyboard files into different repos to help with versioning (#17)
2025-07-21 trying to fix persisting submodule
2025-07-21 working on case submodule issue
2025-07-21 moving things around and making sure everything works correctly
2025-07-21 updating readme
2025-07-22 updating shield keymap
2025-07-23 keymap adjustments
2025-08-19 keyboard fully works if soldered correctly. display works. needs case work still or longer screws
2025-10-31 adding build photos
2025-10-31 fixing photos for github viewing
2025-11-05 updating case
2025-11-05 updating pcb
